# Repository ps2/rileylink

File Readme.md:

# RileyLink

A custom designed Bluetooth Smart (BLE) to Sub-1 GHz module. It can be used to bridge any BLE capable smartphone to the world of Sub-1 GHz devices. 

### Setup

 * There is a [FAQ](https://docs.google.com/document/d/1-KlewmRObpUWCTQSq9EPraN8R-6rCksJS_sRSQSexX0/edit#) covering some questions about installing the firmware.
 * [@loudnate](https://github.com/loudnate) recorded a [setup log](https://docs.google.com/document/d/1-bGBXbxVKOs_tDXi68qiOD7bIT6tQlkQydXn5Q-afLc/edit) of his experience.

### Hardware

See the [hardware](https://github.com/ps2/rileylink/tree/master/hardware) directory for design files to build a RileyLink. The hardware design is released under [Creative Commons Share-alike 3.0](http://creativecommons.org/licenses/by-sa/3.0/).  This board has small parts and will need to be reflow soldered; using a solder-paste stencil is recommended. 

### Order a Pre-Assembed RileyLink
From time-to-time community members do a production run of pre-assembled RileyLink Boards. When they are available you can place an order here [GetRileyLink](https://getrileylink.org/)

### Firmware

The code in the [firmware](https://github.com/ps2/rileylink/tree/master/firmware) directory runs on the RileyLink hardware.  There are two main chips on the RileyLink, and thus two firmware images.

### LED Lights

There are blue and green leds near both chips. The ble113 is on the upper right of the board, and the cc1110 is in the lower middle.  

Blue for the ble113 indicates there are packets received and ready for a phone to pick up. Green means the phone is connected to the ble113.

On the cc1110, I blue is a timer based on/off, letting you know the firmware code is running. Green is toggled when a packet comes in.

The other red LED indicates charging.

### License

The MIT License (MIT)

Copyright (c) 2015 Pete Schwamb

Permission is hereby granted, free of charge, to any person obtaining a copy
of this software and associated documentation files (the "Software"), to deal
in the Software without restriction, including without limitation the rights
to use, copy, modify, merge, publish, distribute, sublicense, and/or sell
copies of the Software, and to permit persons to whom the Software is
furnished to do so, subject to the following conditions:

The above copyright notice and this permission notice shall be included in all
copies or substantial portions of the Software.

THE SOFTWARE IS PROVIDED "AS IS", WITHOUT WARRANTY OF ANY KIND, EXPRESS OR
IMPLIED, INCLUDING BUT NOT LIMITED TO THE WARRANTIES OF MERCHANTABILITY,
FITNESS FOR A PARTICULAR PURPOSE AND NONINFRINGEMENT. IN NO EVENT SHALL THE
AUTHORS OR COPYRIGHT HOLDERS BE LIABLE FOR ANY CLAIM, DAMAGES OR OTHER
LIABILITY, WHETHER IN AN ACTION OF CONTRACT, TORT OR OTHERWISE, ARISING FROM,
OUT OF OR IN CONNECTION WITH THE SOFTWARE OR THE USE OR OTHER DEALINGS IN THE
SOFTWARE.

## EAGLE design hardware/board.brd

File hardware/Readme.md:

# RileyLink Hardware

 * board.sch - circuit schematic
 * board.brd - pcb design file

### Components

The bom.csv file contains a list of parts and quantities

### PCB Assembly

You will have to look at the schematic and the board design in Kicad to know where the parts go, and how they are oriented.

I use a hot-air rework station to solder the BLE113 module, the CC1110 chip and the USB connector. The rest can be soldered with normal soldering station.

### License

The hardware design is released under [Creative Commons Share-alike 3.0](http://creativecommons.org/licenses/by-sa/3.0/).

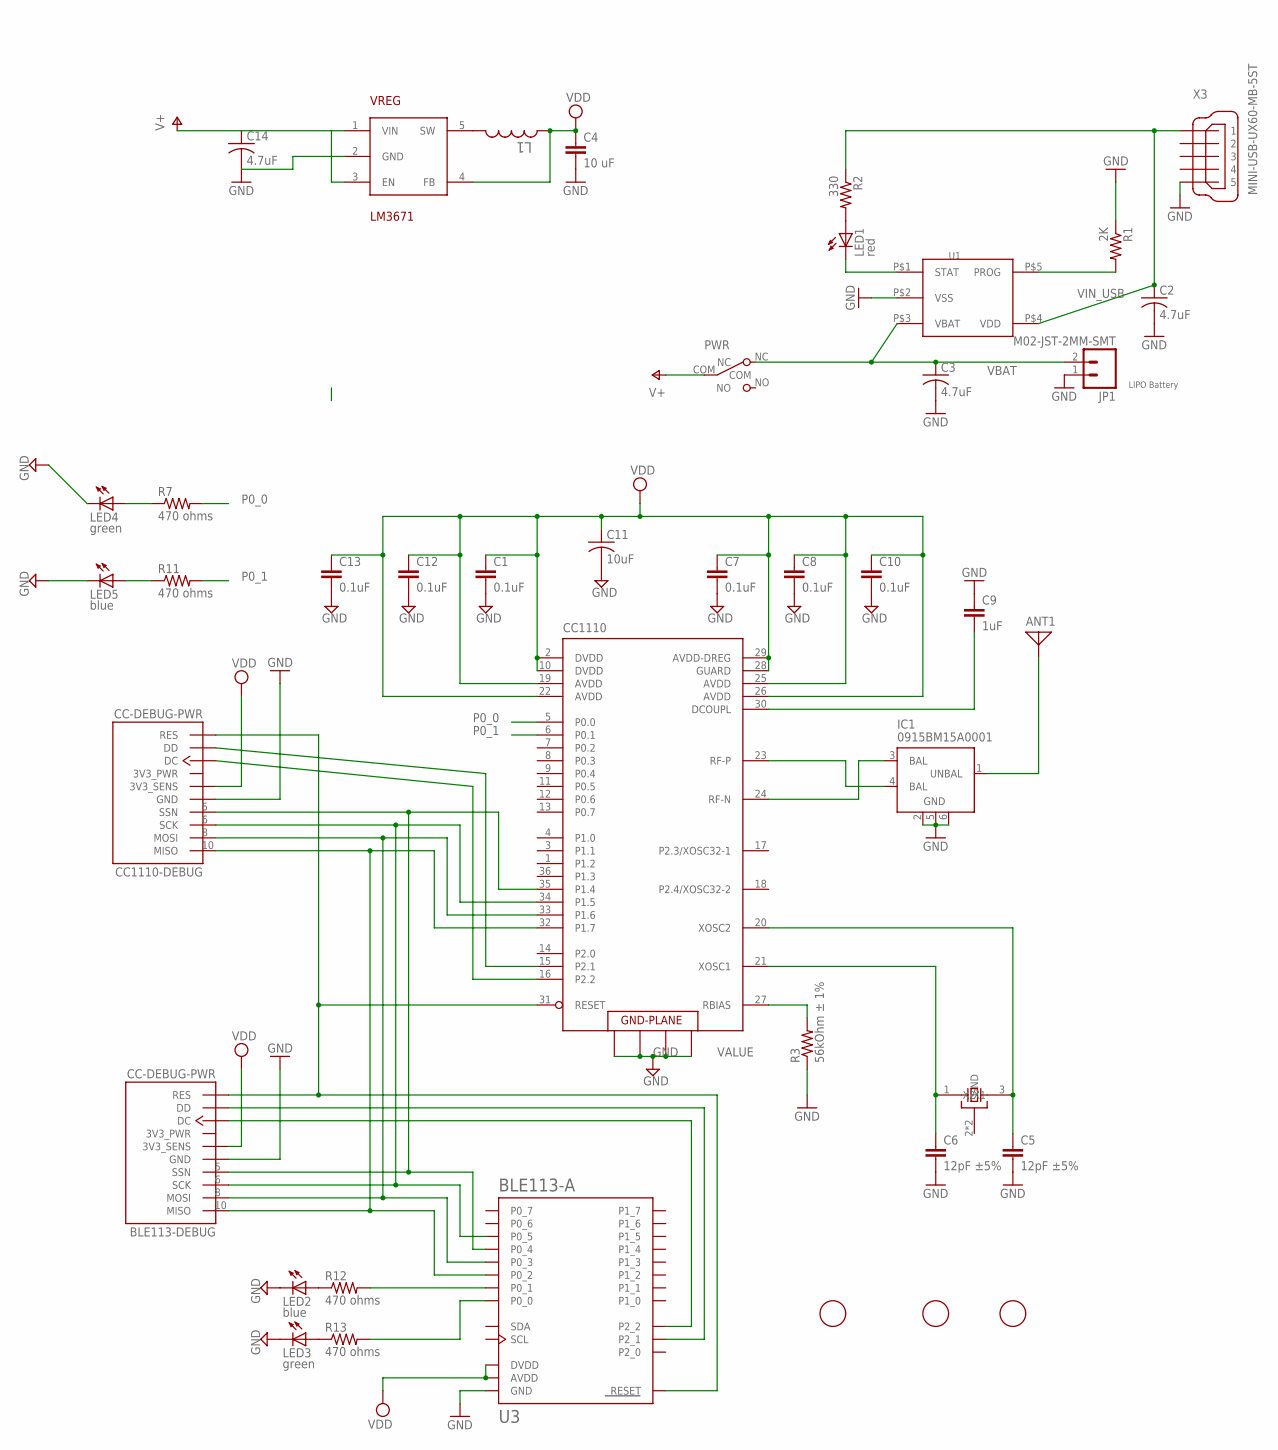
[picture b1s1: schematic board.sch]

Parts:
ANT1: ANTENNA; PAD-01
BLE113-DEBUG: CC-DEBUG-PWR; CC-P05
C1, C7, C8, C10, C12, C13: 0.1uF; C0402
C2, C3, C14: 4.7uF; C0603K
C4: 10 uF; C0805K
C5, C6: 12pF ±5%; C0402K
C9: 1uF; C0402K
C11: 10uF; C0805K
CC1110: CC1110; QLP-36_UPDATE
CC1110-DEBUG: CC-DEBUG-PWR; CC-P05
FID1, FID2, FID3: FIDUCIAL; FIDUCIAL_1MM
IC1: 0915BM15A0001
JP1: M02-JST-2MM-SMT; JST-2-SMD
L1: 2.2 uH; L2825P
LED1: red; SML0603
LED2, LED5: blue; SML0603
LED3, LED4: green; SML0603
PWR: SW_SLIDE; SLIDE_SWITCH_SMD
R1: 2K; R0402
R2: 330; R0402
R3: 56kOhm ± 1%; R0402
R7, R11, R12, R13: 470 ohms; R0402
U1: MCP73831; 5PIN_SOT23
U3: BLE113-A
VREG: LM3671; SOT23-5
X1: 24MHz 8pF 10ppm -20C +70C; CTS_32X25
X3: MINI-USB-UX60-MB-5ST; UX60-MB-5ST

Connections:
DC: CC1110.16 (P2.2), CC1110-DEBUG.3 (DC)
DC_BLE: BLE113-DEBUG.3 (DC), U3.P2_2
DD: CC1110.15 (P2.1), CC1110-DEBUG.4 (DD)
DD_BLE: BLE113-DEBUG.4 (DD), U3.P2_1
GND: BLE113-DEBUG.1 (GND), C1.2, C2.2, C3.2, C4.2, C5.2, C6.2, C7.2, C8.2, C9.1, C10.2, C11.2, C12.2, C13.2, C14.2, CC1110.37 (GND), CC1110.38 (GND), CC1110.39 (GND), CC1110.40 (GND), CC1110-DEBUG.1 (GND), IC1.2 (GND), IC1.5 (GND), IC1.6 (GND), JP1.1 (2), LED2.C, LED3.C, LED4.C, LED5.C, R1.1, R3.1, U1.P$2 (VSS), U3.GND, U3.GND@2 (GND), U3.GND@3 (GND), U3.GND@4 (GND), U3.GND@5 (GND), U3.GND@6 (GND), U3.GND@7 (GND), U3.GND@8 (GND), U3.GND@9 (GND), U3.GND@10 (GND), VREG.2 (GND), X1.2 (GND), X1.4 (GND), X3.5
MISO: BLE113-DEBUG.10 (MISO), CC1110.32 (P1.7), CC1110-DEBUG.10 (MISO), U3.P0_2
MOSI: BLE113-DEBUG.8 (MOSI), CC1110.33 (P1.6), CC1110-DEBUG.8 (MOSI), U3.P0_3
unnamed: LED1.C, U1.P$1 (STAT)
unnamed: R1.2, U1.P$5 (PROG)
unnamed: LED1.A, R2.2
unnamed: CC1110.24 (RF-N), IC1.3 (BAL)
unnamed: CC1110.23 (RF-P), IC1.4 (BAL)
unnamed: ANT1.1, IC1.1 (UNBAL)
unnamed: CC1110.27 (RBIAS), R3.2
unnamed: L1.2, VREG.5 (SW)
unnamed: C9.2, CC1110.30 (DCOUPL)
unnamed: C6.1, CC1110.21 (XOSC1), X1.1 (X1)
unnamed: C5.1, CC1110.20 (XOSC2), X1.3 (X2)
unnamed: LED4.A, R7.1
unnamed: LED5.A, R11.1
unnamed: LED2.A, R12.1
unnamed: LED3.A, R13.1
unnamed: R12.2, U3.P0_1
unnamed: R13.2, U3.P0_0
P0_0: CC1110.5 (P0.0), R7.2
P0_1: CC1110.6 (P0.1), R11.2
RESET: BLE113-DEBUG.7 (RES), CC1110.31 (RESET), CC1110-DEBUG.7 (RES), U3.RESET
SCK: BLE113-DEBUG.6 (SCK), CC1110.34 (P1.5), CC1110-DEBUG.6 (SCK), U3.P0_5
SSN: BLE113-DEBUG.5 (SSN), CC1110.35 (P1.4), CC1110-DEBUG.5 (SSN), U3.P0_4
V+: C14.1, PWR.COM, VREG.1 (VIN), VREG.3 (EN)
VBAT: C3.1, JP1.2 (1), PWR.NC, U1.P$3 (VBAT)
VDD: BLE113-DEBUG.2 (3V3_SENS), C1.1, C4.1, C7.1, C8.1, C10.1, C11.1, C12.1, C13.1, CC1110.2 (DVDD), CC1110.10 (DVDD), CC1110.19 (AVDD), CC1110.22 (AVDD), CC1110.25 (AVDD), CC1110.26 (AVDD), CC1110.28 (GUARD), CC1110.29 (AVDD-DREG), CC1110-DEBUG.2 (3V3_SENS), L1.1, U3.AVDD, U3.DVDD, VREG.4 (FB)
VIN_USB: C2.1, R2.1, U1.P$4 (VDD), X3.1

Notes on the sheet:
LIPO Battery

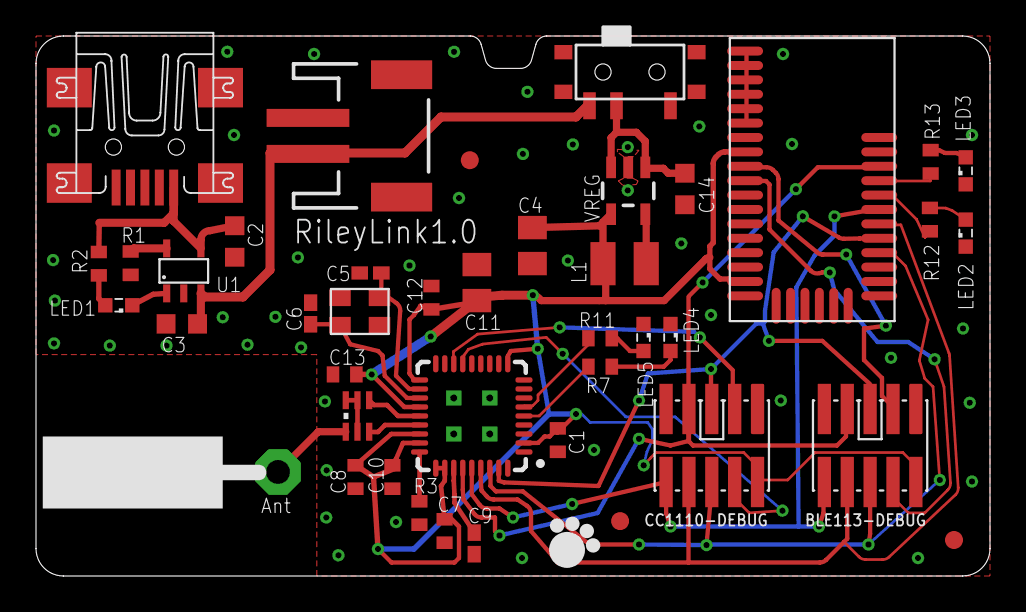
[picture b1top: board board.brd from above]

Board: 2 copper layers, 53.0 x 30.0 mm, 42 parts (0 on the bottom side), 33 nets.

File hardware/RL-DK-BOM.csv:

Digi-Key Part Number,Quantity 1,Customer Reference
587-1227-1-ND,6,100nf
445-7482-1-ND,2,4.7uF
490-3340-1-ND,2,10 uF
490-6196-1-ND,2,12pF ±5%
490-1320-1-ND ,1,1uF
296-38560-1-ND,1,CC1110
MCP73831T-2DCI/OTCT-ND,1,Li-Ion
712-1541-1-ND ,1,Balun
455-1749-1-ND,1,JST Conn
445-1015-1-ND,1,FIXED IND 1.5UH 50MA 700 MOHM
511-1299-1-ND,2,Green Led
LNJ937W8CRACT-ND,2,Blue Led
160-1447-1-ND,1,Red Led
401-2016-1-ND,1,SLIDE_SWITCH_SMD
311-2.0KJRCT-ND ,1,2Kohm 0402
311-330JRCT-ND ,1,330 Ohm 0402
311-56.0KLRCT-ND ,1,56kOhm ± 1% 0402
311-470LRCT-ND,4,470 ohms 0402
311-0.0JRCT-ND ,2,0 Ohm Jumper
296-23904-1-ND,1,REGULATOR
EG4620CT-ND ,1,TACTILE_SWITCH  
1446-1035-1-ND,1,BLE113-A 
644-1052-1-ND,1,Crystal 24MHz 8pF 10ppm -20C +70C
H2959CT-ND,1,MINI-USB-UX60-MB-5ST
609-3695-1-ND ,2,CONN HEADER 10POS DL UNSHRD SMD

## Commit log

2015-05-06 Reconstructed v0.2
2015-05-06 hardware dir
2015-05-22 Adding materials list
2015-05-23 Update with battery, sparkfun notes
2015-05-23 Adding readme
2015-05-23 scale board pic down
2015-05-23 Crop photo
2015-05-23 Adding 3d printer files
2015-05-23 Adding 3d printed case
2015-05-23 update case pic
2015-05-23 Fix coverter part number
2015-05-23 Adding initial skeleton main readme
2015-05-23 Update photo
2015-05-23 Add slide switch part number, and inductor package size
2015-05-23 Add price estimate list
2015-05-23 Adding firmware
2015-05-23 Add license info
2015-06-05 Added Gitter badge
2015-06-08 Remove chip antenna, add fiducials, clean up labels, annotate RileyLink0.3
2015-06-08 Rounded corners, align fiducials
2015-06-11 Fix bias resistor value
2015-06-11 Update value of bias resistor
2015-06-11 Update crystal value and part number
2015-06-13 Add colors to leds, and switch 4.7uF cap from 0402 to 0603 package
2015-06-16 Update C11 to 0805
2015-06-17 Adjust trace per Jason's recommendation
2015-06-17 Update L1 part number
2015-06-23 fixing tx issues
2015-06-25 fix tx bugs
2015-06-26 Adding cc-debugger connection illustration
2015-06-26 Adding smartrf settings
2015-06-26 ignore install.log
2015-06-27 converting app to display nightscout
2015-06-27 Add parts file
2015-06-28 Nav system, config
2015-07-06 comment out mock data generation
2015-07-23 Add illustration to show fitting components in case
2015-07-27 More renaming
2015-07-27 Start working on RileyLink status page
2015-07-27 Start working on list of RileyLinks
2015-07-29 Show devices in rileylink list
2015-07-29 Adding Core Data
2015-07-29 Track ble devices separate from records about how to interact with them
2015-07-30 Show connected state
2015-07-31 display packet log. and add framework for supporting multiple rileylinks
2015-08-01 Instructions for compiling firmware in Windows
2015-08-01 Fixed error when compiling under windows
    Set the default build to output/minimed_rf.hex and added a install option that will build output/minimed_rf.hex and then call cc-tool
2015-08-02 work in progress: interface for sending test packets
2015-08-02 Update Readme.md
    Add note about BGBuild verision requirements.
2015-08-03 Send response if ble client requests it while writing
2015-08-03 Packet log, and packet generator working
2015-08-03 Avoid logging empty reads
2015-08-03 Added a file for install dependancies
2015-08-03 Added the configure line, seems to work now :)
2015-08-03 Missed a line, oops!
2015-08-03 Autoconnect working
2015-08-03 Add timer to reset rx
2015-08-03 Update frequency and channel spacing
2015-08-03 Clarified code
    The construct with multiple ifs and an assignment in an else if was difficult to understand. I think this expresses it more clearly
2015-08-03 added bat file
2015-08-03 Prevent UB when righ/left shifting large char values
    If a symbol value like two 0xFF's come in( symbolInputValue = (symbolInputValue << 8) + value)you will end up with a signed 0xFFFF which is negative and gives Undefined Behaviour later on. Plus it do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
2015-08-04 starting to work on naming
2015-08-04 Setting European frequencies
2015-08-09 Adding pumpID entry
2015-08-09 Keep pumpid textfield visible when keyboard brought up
2015-08-09 Filter out packets from other pumps
2015-08-09 Adding separate tx channel setting
2015-08-09 Adjust ch0 freq, and increase preamble length to 16 bytes
2015-08-10 Updating deprecations
2015-08-10 Modernizing project config
2015-08-10 Cleaning up constraints in the configuration VC
2015-08-10 Raising deployment target and adding launch storyboard
2015-08-10 Sending pump wakeup
2015-08-12 Connection handling updates, cleanup
2015-08-12 set channel
2015-08-13 Adjust freq and preamble length to match latest firmware
2015-08-13 query and display pump model
2015-08-13 rx and tx channels are separate now
2015-08-14 Removing the CBPeripheral category
2015-08-14 Converted CRC table to a const table with data.p
2015-08-15 MySentry pairing tutorial screen
2015-08-15 Setting the channel and improving text entry UI
2015-08-15 Removing packet received notification observer
2015-08-15 Small fix in the CRC code for clarity and performance.
2015-08-15 European frequencies
2015-08-15 will set the European frequencies in a different branch
2015-08-15 set channel to 2 by default
2015-08-16 Adding a podspec for the BLE + Packet files
2015-08-17 Supporting state restoration of the central to minimize scan and discovery
2015-08-17 Show connecting state, and poll battery in pump chat ui
2015-08-18 moving ios app to it's own repository at https://github.com/ps2/rileylink_ios
2015-08-20 Removing podspec, since app no longer lives here
2015-08-22 Modifed data types to use the stdint.h based integers(e.g. uint8_t, int16_t...)
2015-08-22 specify size during assignment from buffers. Now builds with bgbuild 1.3.2. Thanks @loudnate
2015-08-22 Remove notes about using specific bgbuild version.
2015-08-22 Added check for Output folder. Make fails otherwise
2015-08-22 limit another buffer access to one byte
2015-08-24 Changed symbolTable to static const and in code memory not xdata as it will not occupy ram and will never change
    Added crcTable as a static const array instead of generating as it never changes and will not need to occupy code time and memory
2015-08-24 Moved symbolTable back to original memory location. Need to look into why it did not work
2015-08-24 Updated Makefile to make changing params easier(e.g. --verbose)
    Moved const static data to their respective functions(symbolTable, crcTable)
2015-08-25 Marked variables in minimed_rf as volatile as they are modified from within an interrupt
2015-08-26 Update gitignore
2015-09-04 Disconnect after rename, which allows iOS to pick up new name.
2015-09-09 Add bottom restrict for antenna performance
2015-09-12 Move antenna alignment guide to tplace layer
2015-09-12 Add diagram to show placement of reset button
2015-09-12 accidental undo
2015-09-12 move antenna wire silk to tPlace layer
2015-09-12 Update package for TPS63031
2015-09-16 update config file for new smartrf versions
2015-09-21 Update c11 to show it is an 0805 size part
2015-09-21 Update size of C2 to 0603, so you can use same part for C2 and C3
2015-09-29 Settings for 26MHZ crystal
2015-10-06 Update parts for 24MHz in schematic and BOM
2015-10-12 Update frequency for 12pF load capacitors for 24MHzw crystal
2015-10-13 Update loading cap specifications to 12pF
2015-10-22 Specify target, which should reduce likelihood of overwriting the ble113
2015-12-03 Follow SDCC guidlines and mark functions called from an isr as reentrant
2015-12-07 add no-op ble113 firmware so that we can test cc1110 independently
2015-12-26 Adding ble113 firmware for communicating with subg_rfspy over spi
2015-12-26 Update service id
2015-12-28 Send 0x99 for polling command, expect command length prefix from client, and send spi data in chunks of 32
2016-01-01 Fix spi length arg. Not sure the arg is used, as it didn't seem to cause errors, but it was wrong regardless
2016-01-04 another spi rewrite. much better performance now
2016-01-24 Create RL-DK-BOM.csv
    The BOM for 1 RL board, with quantities. Import into Digi-Key by using DK BOM Manager.
2016-01-30 Prevent spi xfer when client writes new command, if client hasn't picked up existing data.
2016-01-30 fix syntax error in last commit
2016-01-30 max txpower for ble113 should be 14, according to docs
2016-01-31 Convert 100nF to 0.1uF since that's how they're sold
2016-01-31 Block do_spi from being entered multiple times due to interrupts
2016-01-31 fix syntax error
2016-02-01 Add timer tick
2016-02-01 Remove hex files
2016-02-20 Remove old cc1110 firmware; replaced by subg_rfspy
2016-02-20 Remove old ble113 firmware; ble113_rfspy is the new firmware for the ble113 side of the RileyLink
2016-02-26 Update for 26mhz xtal
2016-04-18 Fix decoupling cap; it was an error to have it so big. Also, the Digikey BOM had a mistake for its part number.
2016-04-21 reduce amount of solder under cc1110, and label board 0.7p for production run
2016-04-21 Fix description of 1.5uH inductor
2016-04-22 Map all parts to digikey part numbers, unify part names and descriptions.
2016-04-22 Update placement marks to show part orientation
2016-04-30 remove old price estimates
2016-05-10 Remove tactile switch - no digikey equivalent exists
2016-05-18 update blue led
2016-05-27 Initial set of doc updates for writing firmware
2016-06-15 update board image
2016-06-17 Added reference to Bluetooth Smart Software tool
    The Bluetooth Smart Software and SDK v.1.4.2 tool is also required for a successful install.
2016-06-27 Update Readme.md
    Added Link to Order site
2016-07-16 clarify phrasing on account signup
2016-07-23 Updated .stl files
    Added "bumpers" to support USB port to top and bottom and access hole for power switch to top (and also removed hole for battery wires).
2016-09-23 clear output buffer for use as dummy data when receiving data over spi
2016-09-24 Shorten firmware version name
2016-09-30 disable blue led as default, but allow it to be turned back on
2016-11-13 New layout for voltage regulator, add 2 pin header for alternate power.
2016-12-03 Adding higher rated inductor
2016-12-03 update label
2016-12-03 add pawprint
2016-12-03 update bom
2016-12-14 Create Fusion360 Link
2017-01-04 Switch to buck-converter
2017-01-04 update vreg part num
2017-02-11 Add partnames to pcb, and update bom
2017-03-03 Updated Case V2
    Added elements to the case to help the circuit board stay in place for
    charging and for less movement inside.
2017-05-09 Update battery link
2017-05-09 Update oshpark link, and comment about EU pumps
2017-05-10 update getrileylink link
2017-05-10 fix typo
2017-07-01 Added RileyLink ToughCase v1.2
    Added 3D Files for ToughCase
2017-09-16 Formatting
2017-09-16 Rename bgdemo.bgs to main.bgs
2017-11-17 single-response protocol updates
2018-02-10 Only drive SPI while ble client connected
2018-02-10 Adding tshirt design file
2018-04-11 Clear ble output buffer on receipt of new ble command
2018-05-23 Change led mode to off by default
2018-06-02 Add breakout development board
2018-07-26 Revert "Version 2.0"
2019-02-18 Expand clear area around antenna; remove unused u.FL and AUX.PWR connectors.
2019-04-19 Replace gitter with zulipchat
    Replace the gitter badge on the README with a zulipchat badge.
2019-05-19 Update BOM with Digikey replacement parts.
2019-05-19 Update parts list
2019-06-07 Adding PDFs for schematic and board layouts

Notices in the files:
parts and their libraries:
SparkFun-Connectors: Licensing: Creative Commons ShareAlike 4.0 International - https://creativecommons.org/licenses/by-sa/4.0
parts: Package design from "pretty-eagle-libs" at https://github.com/esden/pretty-eagle-libs/blob/master/pel_misc.lbr by @esden at Github. (CC-BY-SA-3.0)
